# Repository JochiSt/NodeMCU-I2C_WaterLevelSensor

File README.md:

# NodeMCU-I2C_WaterLevelSensor
A capacitive water level sensor based on NE555 + AVR I2C slave + NodeMCU Wifi adapter to map I2C to UDP

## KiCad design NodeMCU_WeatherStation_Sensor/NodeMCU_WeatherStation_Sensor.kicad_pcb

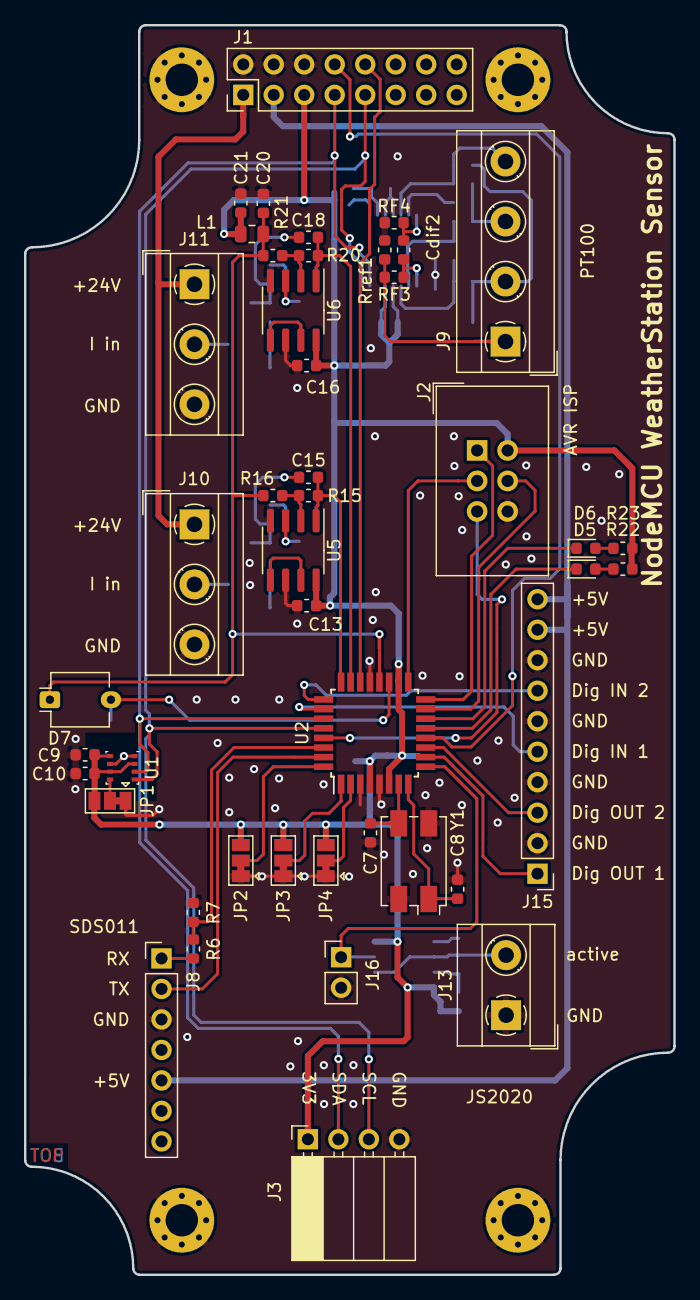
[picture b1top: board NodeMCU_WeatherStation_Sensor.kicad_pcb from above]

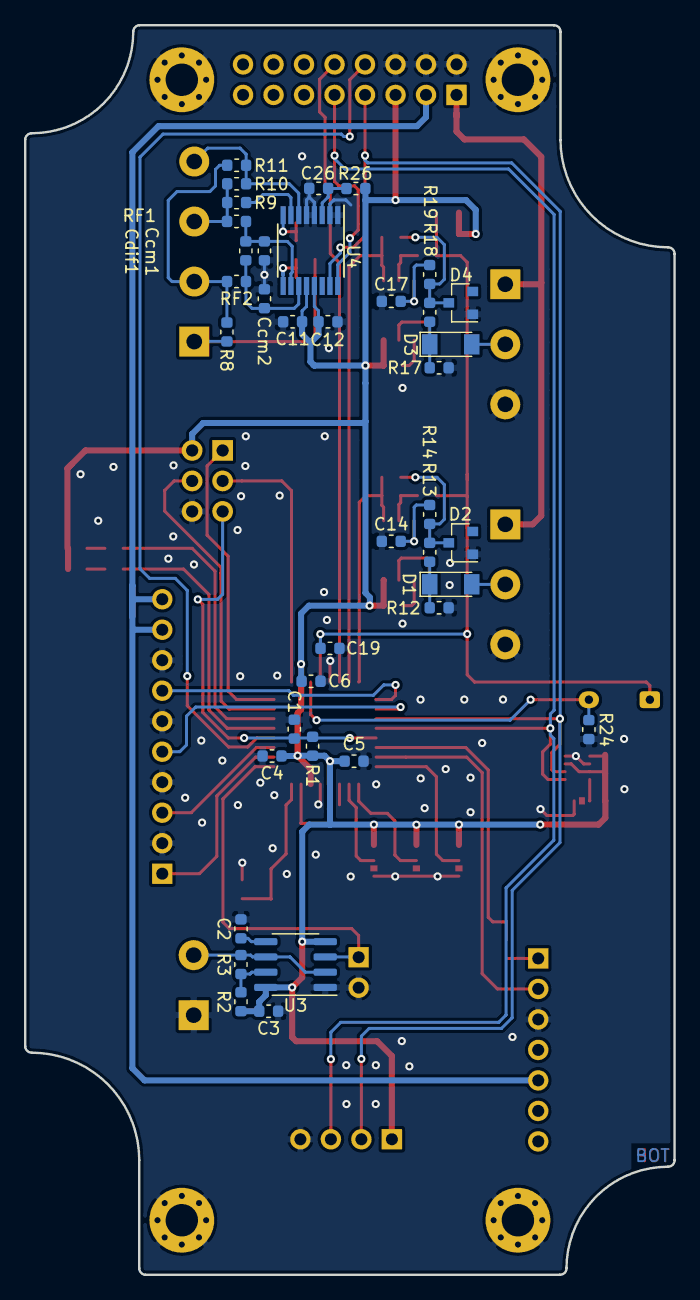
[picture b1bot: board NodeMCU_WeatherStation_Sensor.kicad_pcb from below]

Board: 2 copper layers, 54.1 x 104.1 mm, 87 parts (38 on the bottom side), 59 nets.

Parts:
C1, C2, C3, C4, C5, C6, C9, C10, C11, C12, C13, C14, C15, C16, C17, C18, C19, C20, C21, C26: 100n; C_0603_1608Metric
C7, C8: 22p; C_0603_1608Metric
Ccm1, Ccm2: 10n; C_0603_1608Metric
Cdif1, Cdif2: 100n; C_0603_1608Metric
D1, D3: LL4148; D_MiniMELF
D2, D4: BZX84Cxx; D_SOT-23_ANK
D5, D6: LED; LED_0603_1608Metric
D7: BPW34; Osram_DIL2_4.3x4.65mm_P5.08mm
H3, H4, H5, H6: MountingHole_Pad; MountingHole_2.7mm_M2.5_Pad_Via
J1: Conn_02x08_Odd_Even; PinHeader_2x08_P2.54mm_Vertical
J2: AVR-ISP-6; IDC-Header_2x03_P2.54mm_Vertical
J3: Conn_01x04; PinSocket_1x04_P2.54mm_Horizontal
J8: Conn_01x07; PinHeader_1x07_P2.54mm_Vertical
J9: Screw_Terminal_01x04; TerminalBlock_MetzConnect_Type055_RT01504HDWU_1x04_P5.00mm_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
J10, J11: Screw_Terminal_01x03; TerminalBlock_MetzConnect_Type055_RT01503HDWU_1x03_P5.00mm_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
J13: Screw_Terminal_01x02; TerminalBlock_MetzConnect_Type055_RT01502HDWU_1x02_P5.00mm_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
J15: Conn_01x10; PinHeader_1x10_P2.54mm_Vertical
J16: Conn_01x02; PinHeader_1x02_P2.54mm_Vertical
JP1, JP2, JP3, JP4: SolderJumper_3_Bridged12; SolderJumper-3_P1.3mm_Bridged12_Pad1.0x1.5mm
L1: L; L_0805_2012Metric
R1, R24, R26: 10k; R_0603_1608Metric
R2: 330k; R_0603_1608Metric
R3: 680k; R_0603_1608Metric
R6: 1k; R_0603_1608Metric
R7, R22, R23: 2k2; R_0603_1608Metric
R8, R9, R10, R11: n.b. (0R); R_0603_1608Metric
R12, R17: 160; R_0603_1608Metric
R13, R14, R18, R19: 100k; R_0603_1608Metric
R15, R20: 15k; R_0603_1608Metric
R16, R21: 75k; R_0603_1608Metric
RF1, RF2, RF3, RF4: 470; R_0603_1608Metric
Rref1: 1k65; R_0603_1608Metric
U1: BME280; Bosch_LGA-8_2.5x2.5mm_P0.65mm_ClockwisePinNumbering
U2: ATmega328P-AU; TQFP-32_7x7mm_P0.8mm
U3: TLC555CD; SOIC-8_3.9x4.9mm_P1.27mm
U4: ADS122C04IPW; TSSOP-16_4.4x5mm_P0.65mm
U5, U6: LT1492; SOIC-8_3.9x4.9mm_P1.27mm
Y1: 16MHz; Crystal_SMD_EuroQuartz_MQ-4Pin_7.0x5.0mm

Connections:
+3V3: C3.2, C4.1, C5.1, C6.1, C9.1, C10.1, C11.1, C12.1, C13.1, C16.1, C21.1, J1.5, J2.2, J3.1, JP1.3, JP2.3, JP3.3, JP4.3, L1.2, R1.1, R2.1, R22.1, R23.1, R26.1, U1.2, U1.6, U1.8, U2.4, U2.6, U2.18, U3.4, U3.8, U4.12, U4.13, U5.8, U6.8
+5V: J1.3, J8.5, J15.9, J15.10
+24V: J1.1, J10.1, J11.1
/4to20in 1/4to20input: D1.1, R12.1, R13.1
/4to20in 1/Vref: C19.1, C20.1, D7.1, L1.1, R16.2, R21.2, U2.20
/4to20in 2/4to20input: D3.1, R17.1, R18.1
/AIN: J1.10, U2.22
/I2C Water Sensor/ADC0: C15.2, R15.1, U2.24, U5.1
/I2C Water Sensor/ADC1: C18.2, R20.1, U2.23, U6.1
/I2C Water Sensor/ADC2: D7.2, R24.1, U2.19
/I2C Water Sensor/ADDR0: JP2.2, U2.32
/I2C Water Sensor/ADDR1: JP3.2, U2.1
/I2C Water Sensor/ADDR2: JP4.2, U2.2
/I2C Water Sensor/DigIn1: J15.5, U2.26
/I2C Water Sensor/DigIn2: J15.7, U2.25
/I2C Water Sensor/DigOut1: J15.1, U2.10
/I2C Water Sensor/DigOut2: J15.3, U2.11
/I2C Water Sensor/FREQIN: J16.1, U2.9, U3.3
/I2C Water Sensor/MISO: J2.1, U2.16
/I2C Water Sensor/MOSI: J2.4, U2.15
/I2C Water Sensor/RESET: C1.1, J2.5, R1.2, U2.29
/I2C Water Sensor/RXD: R6.1, R7.1, U2.30
/I2C Water Sensor/SCK: J2.3, U2.17
/I2C Water Sensor/TXD: J8.2, U2.31
/PT100 I2C readout/AIN0: Ccm2.2, Cdif1.1, RF2.1, U4.11
/PT100 I2C readout/AIN1: Ccm1.1, Cdif1.2, RF1.1, U4.10
/PT100 I2C readout/AIN2: R9.1, U4.7
/PT100 I2C readout/AIN3: J9.4, R10.1, R11.1, U4.6
/SCL: J1.9, J3.3, U1.4, U2.28, U4.16
/SDA: J1.7, J3.2, U1.3, U2.27, U4.15
/Sensor Front End/THR: J13.2, R3.2, U3.2, U3.6
/WS2812: J1.8, U2.12
GND: C1.2, C2.2, C3.1, C4.2, C5.2, C6.2, C7.2, C8.2, C9.2, C10.2, C11.2, C12.2, C13.2, C14.1, C16.2, C17.1, C19.2, C20.2, C21.2, C26.2, Ccm1.2, Ccm2.1, D2.2, D4.2, H3.1, H4.1, H5.1, H6.1, J1.2, J1.4, J1.6, J2.6, J3.4, J8.3, J10.3, J11.3, J13.1, J15.2, J15.4, J15.6, J15.8, J16.2, JP1.1, JP2.1, JP3.1, JP4.1, R7.2, R12.2, R17.2, R24.2, RF4.2, Rref1.1, U1.1, U1.7, U2.3, U2.5, U2.21, U3.1, U4.1, U4.2, U4.4, U4.5, U5.4, U5.6, U6.4, U6.6, Y1.2, Y1.4
unnamed: C2.1, U3.5
unnamed: C7.1, U2.7, Y1.3
unnamed: C8.1, U2.8, Y1.1
unnamed: C14.2, R14.2, U5.3
unnamed: C15.1, D2.1, R13.2, R14.1
unnamed: C17.2, R19.2, U6.3
unnamed: C18.1, D4.1, R18.2, R19.1
unnamed: C26.1, R26.2, U4.3
unnamed: Cdif2.1, RF3.1, U4.9
unnamed: Cdif2.2, RF4.1, U4.8
unnamed: D1.2, J10.2
unnamed: D3.2, J11.2
unnamed: D5.1, U2.13
unnamed: D5.2, R22.2
unnamed: D6.1, U2.14
unnamed: D6.2, R23.2
unnamed: J8.1, R6.2
unnamed: J9.1, R8.1, RF3.2, Rref1.2
unnamed: J9.2, R8.2, R11.2, RF2.2
unnamed: J9.3, R9.2, R10.2, RF1.2
unnamed: JP1.2, U1.5
unnamed: R2.2, R3.1, U3.7
unnamed: R15.2, R16.1, U5.2
unnamed: R20.2, R21.1, U6.2
unnamed: U5.5, U5.7
unnamed: U6.5, U6.7

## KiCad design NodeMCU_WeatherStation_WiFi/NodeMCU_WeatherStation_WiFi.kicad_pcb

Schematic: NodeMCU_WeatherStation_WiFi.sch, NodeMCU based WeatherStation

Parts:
C9, C10, C22, C24, C25: 100n; C_0603_1608Metric
C23: 4u7; CP_Elec_10x10
D1, D2, D3, D4: WS2812B; LED_WS2812B_PLCC4_5.0x5.0mm_P3.2mm
D8: SM4001; D_MELF
H3, H4, H5, H6: MountingHole_Pad; MountingHole_2.7mm_M2.5_Pad_Via
J1: Conn_02x08_Odd_Even; PinHeader_2x08_P2.54mm_Vertical
J4, J5: Conn_01x04; PinSocket_1x04_P2.54mm_Horizontal
J12, J14: Screw_Terminal_01x02; TerminalBlock_MetzConnect_Type055_RT01502HDWU_1x02_P5.00mm_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
JP1: SolderJumper_3_Bridged12; SolderJumper-3_P1.3mm_Bridged12_Pad1.0x1.5mm
Q1: BSS138; SOT-23
R1, R2: 10k; R_0603_1608Metric
R3: 100; R_0603_1608Metric
R6: n.b.; R_0603_1608Metric
U1: BME280; Bosch_LGA-8_2.5x2.5mm_P0.65mm_ClockwisePinNumbering
U7: R-785.0-0.5; Converter_DCDC_RECOM_R-78E-0.5_THT

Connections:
+5V: C24.1, C25.1, D1.1, D2.1, D3.1, D4.1, D8.2 (A), J1.3, J14.1, R2.1, U7.3 (OUT); also elsewhere on the board
+24V: C22.1, C23.1, D8.1 (K), J1.1, J12.1, U7.1 (IN)
/AIN: J1.10
/NodeMCU/WS2812_NodeMCU: R6.2; also elsewhere on the board
/SCL: J1.9, J4.3, J5.3, U1.4 (SCK); also elsewhere on the board
/SDA: J1.7, J4.2, J5.2, U1.3 (SDI); also elsewhere on the board
/WS2812: J1.8, Q1.2, R1.2, R6.1
GND: C9.2, C10.2, C22.2, C23.2, C24.2, C25.2, D1.3, D2.3, D3.3, D4.3, H3.1, H4.1, H5.1, H6.1, J1.2, J1.4, J1.6, J4.4, J5.4, J12.2, J14.2, JP1.1 (A), U1.1 (GND), U1.7 (GND), U7.2 (GND); also elsewhere on the board
unnamed: D1.2, D2.4
unnamed: D1.4, R3.1
unnamed: D2.2, D3.4
unnamed: D3.2, D4.4
unnamed: JP1.2 (C), U1.5 (SDO)
unnamed: Q1.3, R2.2, R3.2

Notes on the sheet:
I2C Input / Output both parallel
input voltage 6V5 - 32V fixed 5V 500mA output
External 5V supply
External 24V supply
MASTER
Housing RND 455-00208
WS28B12 for displaying some Status

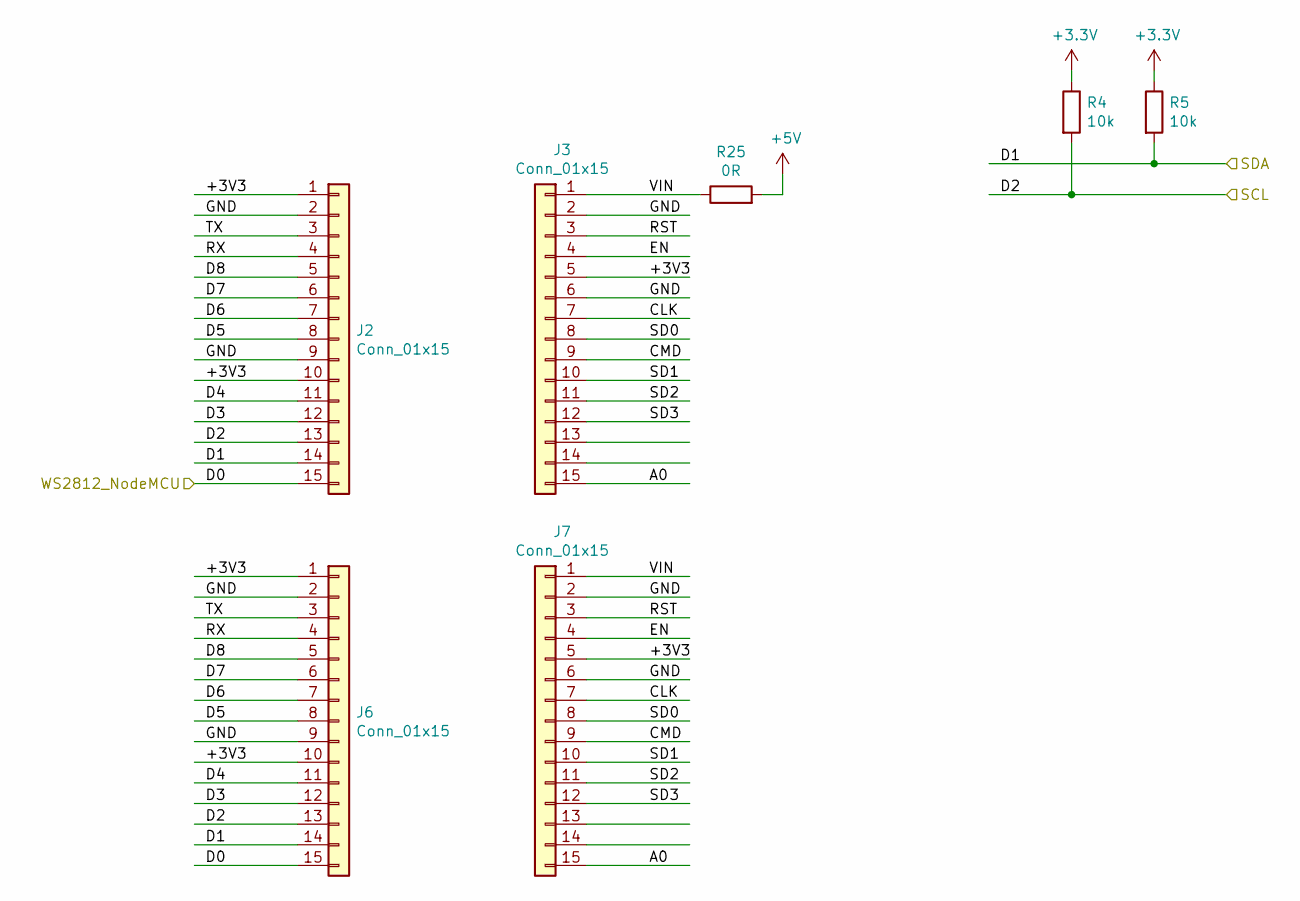
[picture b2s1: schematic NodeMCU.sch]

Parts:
J2, J3, J6, J7: Conn_01x15; PinSocket_1x15_P2.54mm_Vertical
R4, R5: 10k; R_0603_1608Metric
R25: 0R; R_0603_1608Metric

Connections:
+5V: R25.2; also elsewhere on the board
/NodeMCU/A0: J3.15, J7.15
/NodeMCU/CLK: J3.7, J7.7
/NodeMCU/CMD: J3.9, J7.9
/NodeMCU/D3: J2.12, J6.12
/NodeMCU/D4: J2.11, J6.11
/NodeMCU/D5: J2.8, J6.8
/NodeMCU/D6: J2.7, J6.7
/NodeMCU/D7: J2.6, J6.6
/NodeMCU/D8: J2.5, J6.5
/NodeMCU/EN: J3.4, J7.4
/NodeMCU/RST: J3.3, J7.3
/NodeMCU/RX: J2.4, J6.4
/NodeMCU/SD0: J3.8, J7.8
/NodeMCU/SD1: J3.10, J7.10
/NodeMCU/SD2: J3.11, J7.11
/NodeMCU/SD3: J3.12, J7.12
/NodeMCU/TX: J2.3, J6.3
/NodeMCU/VIN: J3.1, J7.1, R25.1
/NodeMCU/WS2812_NodeMCU: J2.15, J6.15; also elsewhere on the board
/SCL: J2.13, J6.13, R4.2; also elsewhere on the board
/SDA: J2.14, J6.14, R5.2; also elsewhere on the board
GND: J2.2, J2.9, J3.2, J3.6, J6.2, J6.9, J7.2, J7.6; also elsewhere on the board

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
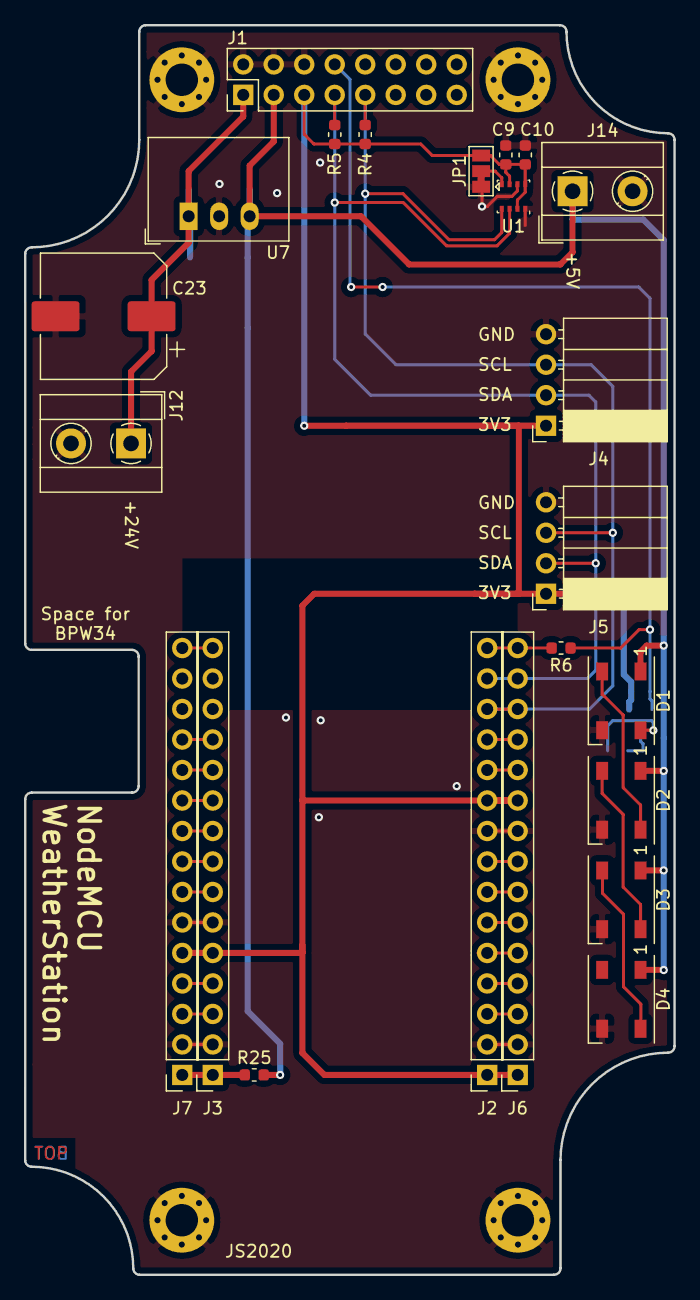
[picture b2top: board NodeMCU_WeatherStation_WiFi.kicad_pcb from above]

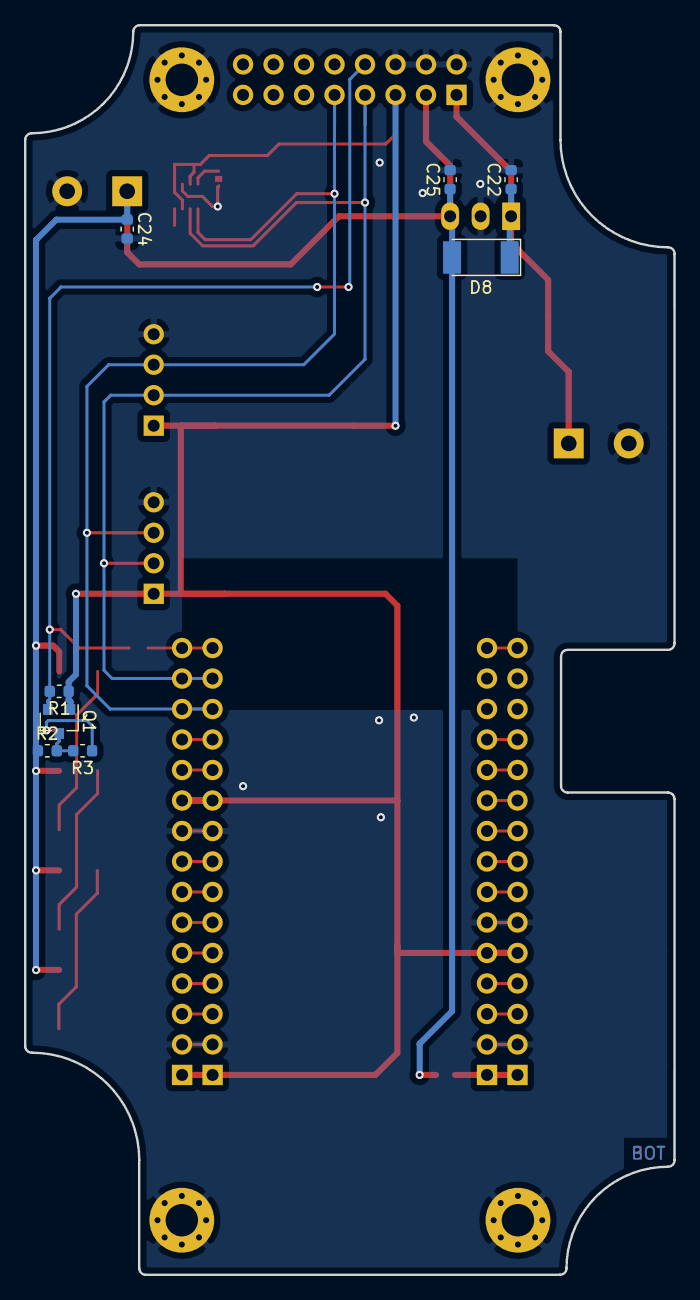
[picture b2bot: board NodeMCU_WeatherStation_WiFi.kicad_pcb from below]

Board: 2 copper layers, 54.1 x 104.1 mm, 35 parts (8 on the bottom side), 32 nets.

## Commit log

2020-05-22 Create LICENSE
2020-05-22 initial commit of partial routed board
2020-05-22 added main schematic
2020-06-04 added 4-20mA input and PT100 readout
2020-06-08 added BPW34 for measurement of light intensity
2020-06-10 added digital output, 24V to 5V voltage regulator
2020-06-10 cleaned up PCB labels
2020-06-10 changed to 3.2mm holes for mounting the PCB
2020-06-10 added schematic
2020-06-10 added GERBER
2020-06-16 added proper reset to PT100 readout
2020-06-22 included address jumper for AVR, which makes it easier to use multiple of these boards at the same I2C bus.
2022-01-19 include latest changes
    latest changes to design
2022-01-19 about to split into two projects
2022-01-19 splitted into Sensor Front End and WiFi connection
2022-01-25 added *.zip files
